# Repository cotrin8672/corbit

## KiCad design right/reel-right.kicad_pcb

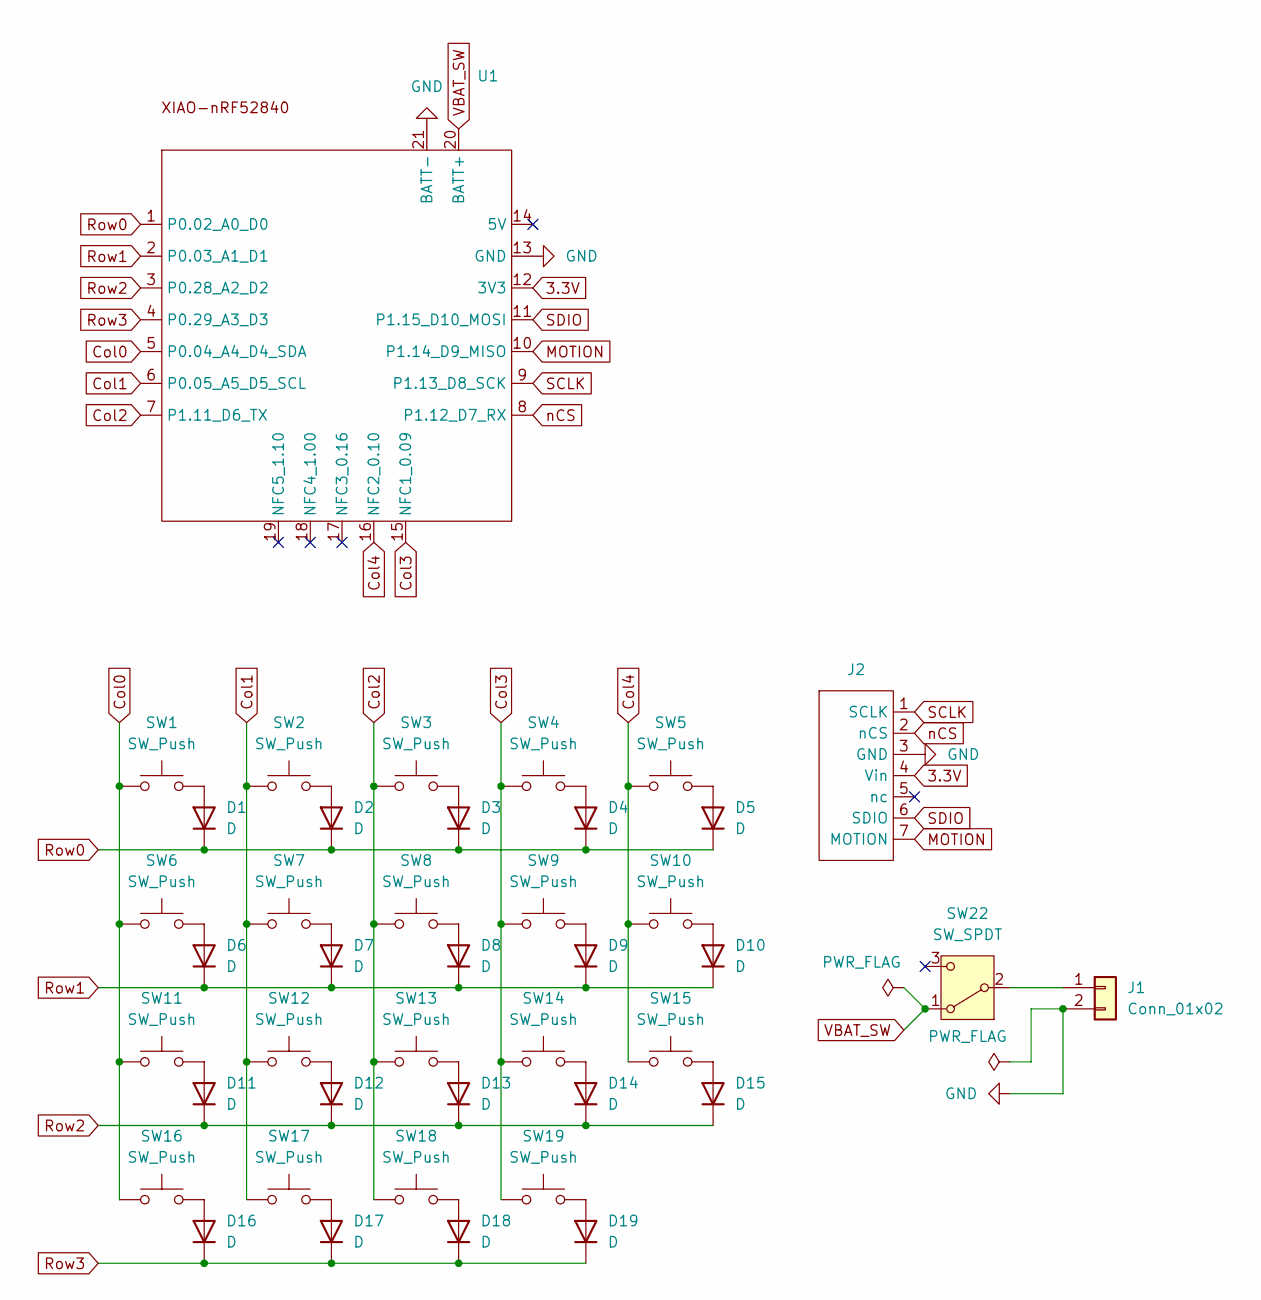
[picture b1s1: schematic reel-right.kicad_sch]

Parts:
D1, D2, D3, D4, D5, D6, D7, D8, D9, D10, D11, D12, D13, D14, D15, D16, D17, D18, D19: D; D_SOD-123
J1: Conn_01x02; JST_PH_S2B-PH-K_1x02_P2.00mm_Horizontal
J2: pmw3610_connector
SW1, SW2, SW3, SW4, SW5, SW6, SW7, SW8, SW9, SW10, SW11, SW12, SW13, SW14, SW15, SW16, SW17, SW18, SW19: SW_Push; SW_Hotswap_Kailh_Choc_V1_1.00u-NoClickHole
SW22: SW_SPDT; SW_SPDT_PCM12
U1: XIAO_nRF52840_wBAT_wNFC_1

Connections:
3.3V: J2.4 (Vin), U1.12 (3V3)
Col0: SW1.1, SW6.1, SW11.1, SW16.1, U1.5 (P0.04_A4_D4_SDA)
Col1: SW2.1, SW7.1, SW12.1, SW17.1, U1.6 (P0.05_A5_D5_SCL)
Col2: SW3.1, SW8.1, SW13.1, SW18.1, U1.7 (P1.11_D6_TX)
Col3: SW4.1, SW9.1, SW14.1, SW19.1, U1.15 (NFC1_0.09)
Col4: SW5.1, SW10.1, SW15.1, U1.16 (NFC2_0.10)
GND: J1.2, J2.3 (GND), U1.13 (GND), U1.21 (BATT-)
MOTION: J2.7 (MOTION), U1.10 (P1.14_D9_MISO)
unnamed: D1.2 (A), SW1.2
unnamed: D2.2 (A), SW2.2
unnamed: D3.2 (A), SW3.2
unnamed: D4.2 (A), SW4.2
unnamed: D5.2 (A), SW5.2
unnamed: D6.2 (A), SW6.2
unnamed: D7.2 (A), SW7.2
unnamed: D8.2 (A), SW8.2
unnamed: D9.2 (A), SW9.2
unnamed: D10.2 (A), SW10.2
unnamed: D11.2 (A), SW11.2
unnamed: D12.2 (A), SW12.2
unnamed: D13.2 (A), SW13.2
unnamed: D14.2 (A), SW14.2
unnamed: D15.2 (A), SW15.2
unnamed: D16.2 (A), SW16.2
unnamed: D17.2 (A), SW17.2
unnamed: D18.2 (A), SW18.2
unnamed: D19.2 (A), SW19.2
unnamed: J1.1, SW22.2 (B)
Row0: D1.1 (K), D2.1 (K), D3.1 (K), D4.1 (K), D5.1 (K), U1.1 (P0.02_A0_D0)
Row1: D6.1 (K), D7.1 (K), D8.1 (K), D9.1 (K), D10.1 (K), U1.2 (P0.03_A1_D1)
Row2: D11.1 (K), D12.1 (K), D13.1 (K), D14.1 (K), D15.1 (K), U1.3 (P0.28_A2_D2)
Row3: D16.1 (K), D17.1 (K), D18.1 (K), D19.1 (K), U1.4 (P0.29_A3_D3)
SCLK: J2.1 (SCLK), U1.9 (P1.13_D8_SCK)
SDIO: J2.6 (SDIO), U1.11 (P1.15_D10_MOSI)
VBAT_SW: SW22.1 (A), U1.20 (BATT+)
nCS: J2.2 (nCS), U1.8 (P1.12_D7_RX)

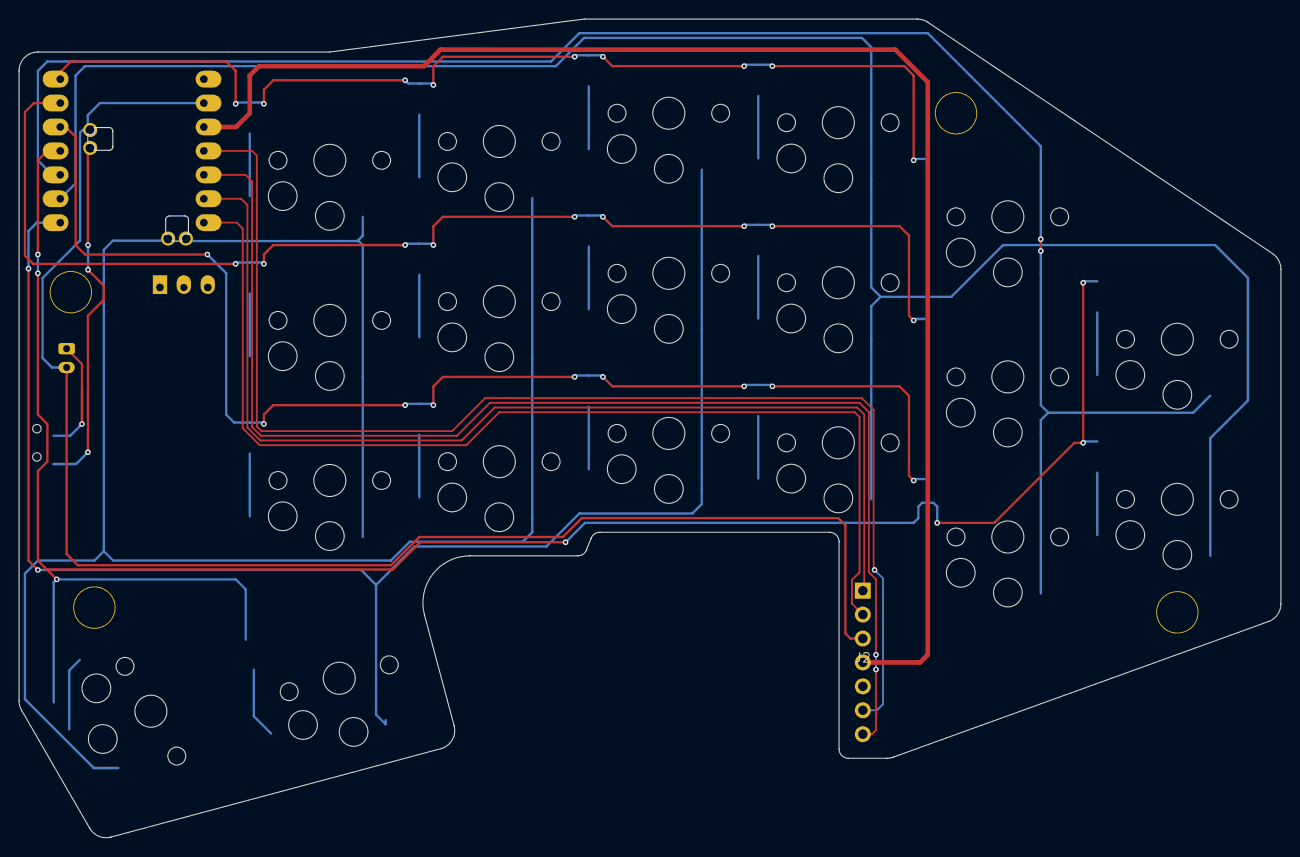
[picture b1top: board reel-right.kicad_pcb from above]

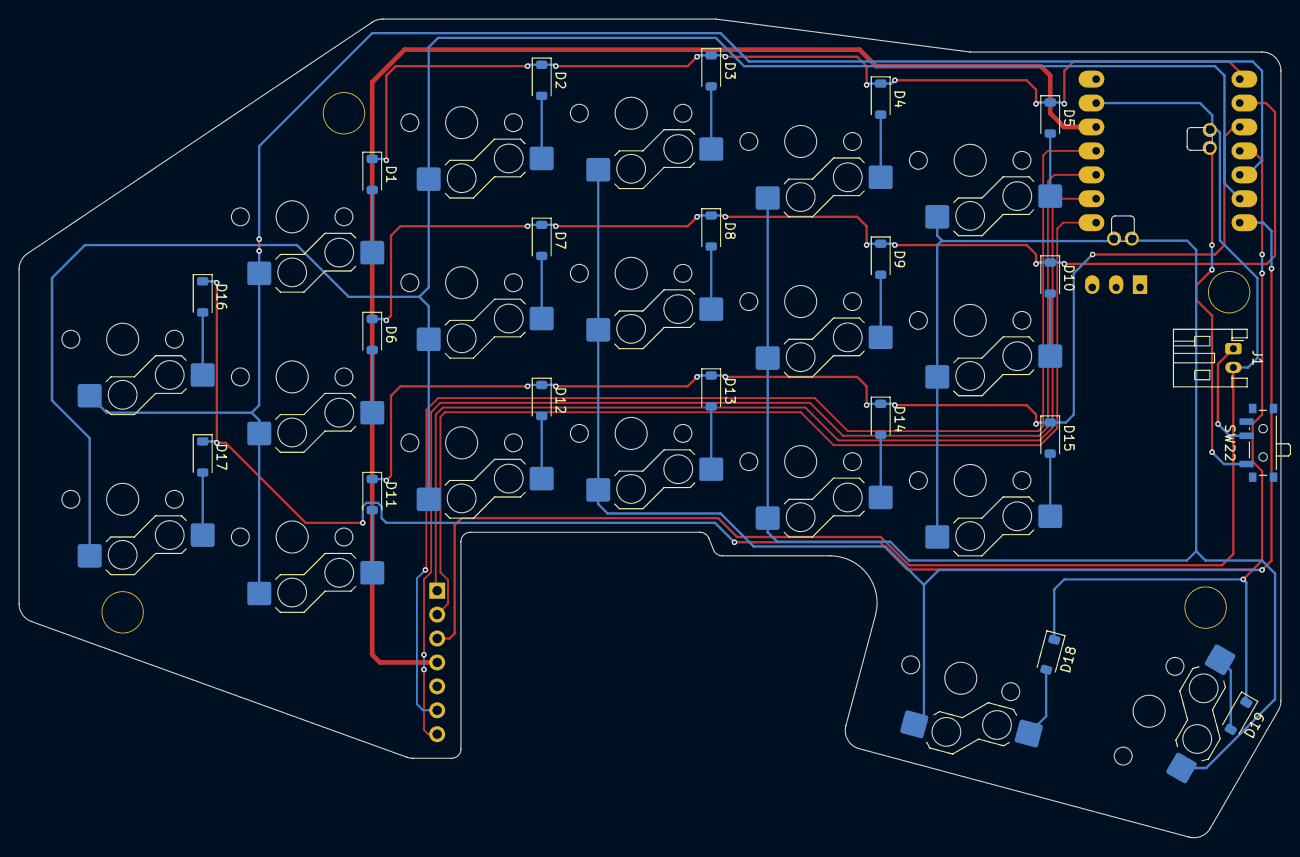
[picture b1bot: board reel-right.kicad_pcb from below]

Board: 2 copper layers, 134.0 x 86.9 mm, 46 parts (21 on the bottom side), 36 nets.

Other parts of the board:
Ref**: Val**; m2_Spacer_Hole
Ref**#2, Ref**#3, Ref**#4: Val**; m2_Spacer_Hole

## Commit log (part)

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2026-05-19 add: gitignore
2026-05-20 fix sch
2026-06-19 fixed direction of diode and slide switch
2026-06-21 rename to ReeL
2026-06-21 edit
2026-06-21 fix footprint
2026-06-28 Update left PCB routing
2026-06-28 Update left PCB layout
2026-06-28 Update left and right PCB layouts
2026-06-29 Update right PCB layout
2026-06-30 Update left and right board assets
